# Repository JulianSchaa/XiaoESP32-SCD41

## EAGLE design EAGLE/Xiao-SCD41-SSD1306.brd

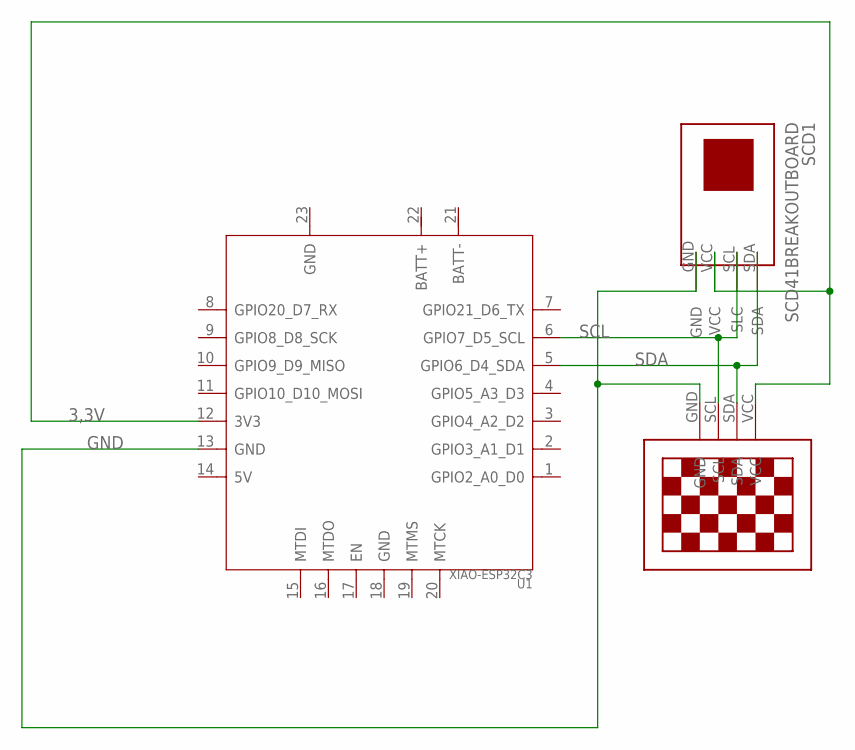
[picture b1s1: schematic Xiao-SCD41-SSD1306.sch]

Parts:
SCD1: SCD41BREAKOUTBOARD; SCD41
U1: XIAO-ESP32C3; XIAO-ESP32C3-MODULE14P-2.54-21X17.8MM
U$1: 13"OLED13"OLED; 1.3"OLED

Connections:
3,3V: SCD1.VCC, U1.12 (3V3), U$1.VCC
GND: SCD1.GND, U1.13 (GND), U$1.GND
SCL: SCD1.SCL (SLC), U1.6 (GPIO7_D5_SCL), U$1.SCL
SDA: SCD1.SDA, U1.5 (GPIO6_D4_SDA), U$1.SDA

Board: 2 copper layers, 3 parts (0 on the bottom side), 4 nets, no tracks yet.

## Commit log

2024-12-19 Rename XIAO-ESP32C3-v1.2_SCH-PCB.zip to Eagle-Lib-XIAO-ESP32C3.zip
2024-12-19 Create test
